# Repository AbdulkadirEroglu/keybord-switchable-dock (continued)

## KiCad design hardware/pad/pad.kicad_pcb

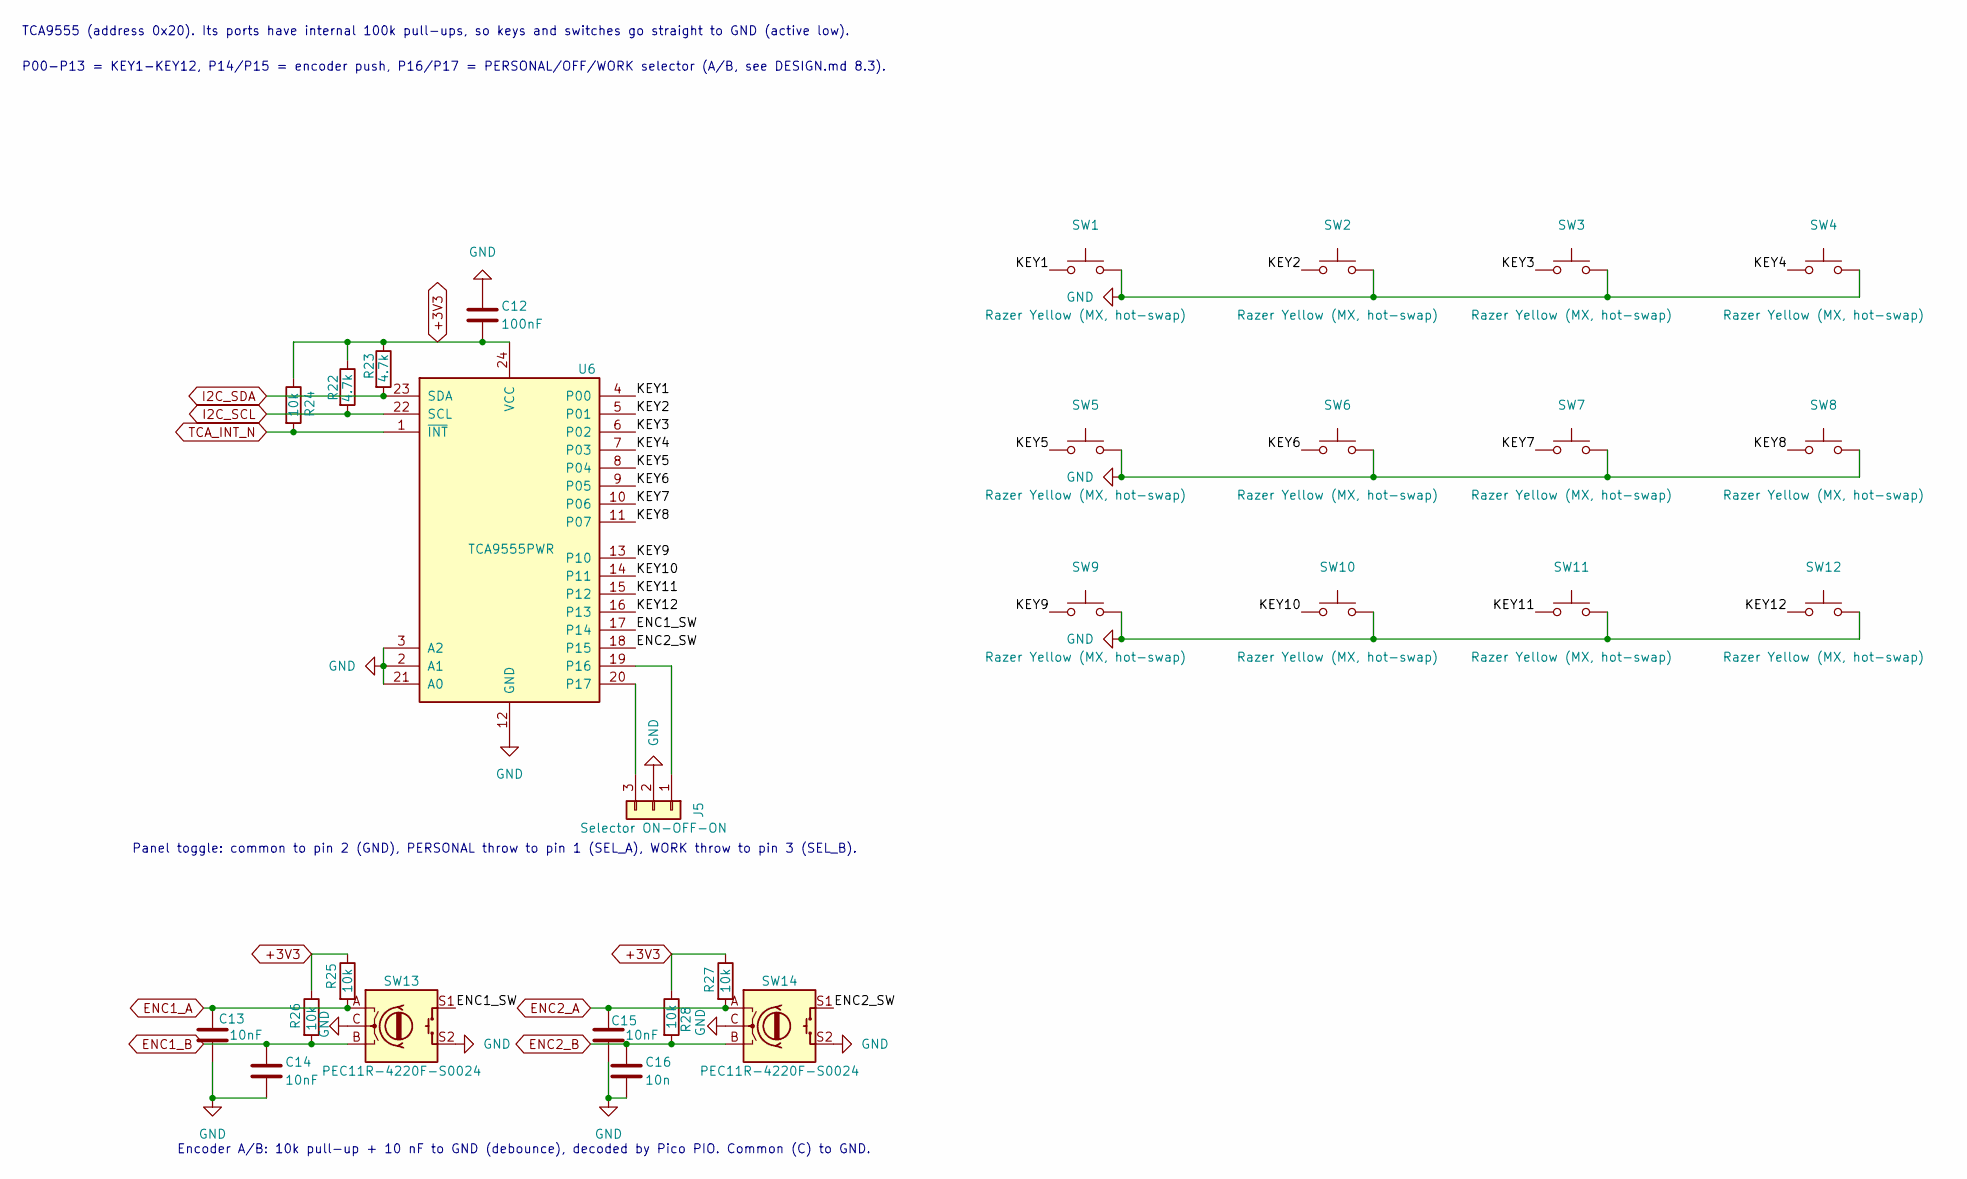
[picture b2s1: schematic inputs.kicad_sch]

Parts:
C12: 100nF; C_0805_2012Metric_Pad1.18x1.45mm_HandSolder
C13, C14, C15: 10nF; C_0805_2012Metric_Pad1.18x1.45mm_HandSolder
C16: 10n; C_0805_2012Metric_Pad1.18x1.45mm_HandSolder
J5: Selector ON-OFF-ON; JST_XH_B3B-XH-A_1x03_P2.50mm_Vertical
R22, R23: 4.7k; R_0805_2012Metric_Pad1.20x1.40mm_HandSolder
R24, R25, R26, R27, R28: 10k; R_0805_2012Metric_Pad1.20x1.40mm_HandSolder
SW1, SW2, SW3, SW4, SW5, SW6, SW7, SW8, SW9, SW10, SW11, SW12: Razer Yellow (MX, hot-swap); SW_MX_Hotswap_Kailh
SW13, SW14: PEC11R-4220F-S0024; RotaryEncoder_Bourns_PEC11R-4xxxF-S_Vertical
U6: TCA9555PWR; TSSOP-24_4.4x7.8mm_P0.65mm

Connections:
+3V3: C12.2, R22.1, R23.1, R24.1, R25.1, R26.1, R27.1, R28.1, U6.24 (VCC); also elsewhere on the board
/INPUTS/ENC1_SW: SW13.S1, U6.17 (P14)
/INPUTS/ENC2_SW: SW14.S1, U6.18 (P15)
/INPUTS/KEY1: SW1.1, U6.4 (P00)
/INPUTS/KEY2: SW2.1, U6.5 (P01)
/INPUTS/KEY3: SW3.1, U6.6 (P02)
/INPUTS/KEY4: SW4.1, U6.7 (P03)
/INPUTS/KEY5: SW5.1, U6.8 (P04)
/INPUTS/KEY6: SW6.1, U6.9 (P05)
/INPUTS/KEY7: SW7.1, U6.10 (P06)
/INPUTS/KEY8: SW8.1, U6.11 (P07)
/INPUTS/KEY9: SW9.1, U6.13 (P10)
/INPUTS/KEY10: SW10.1, U6.14 (P11)
/INPUTS/KEY11: SW11.1, U6.15 (P12)
/INPUTS/KEY12: SW12.1, U6.16 (P13)
ENC1_A: C13.1, R25.2, SW13.A; also elsewhere on the board
ENC1_B: C14.1, R26.2, SW13.B; also elsewhere on the board
ENC2_A: C15.1, R27.2, SW14.A; also elsewhere on the board
ENC2_B: C16.1, R28.2, SW14.B; also elsewhere on the board
GND: C12.1, C13.2, C14.2, C15.2, C16.2, J5.2, SW1.2, SW2.2, SW3.2, SW4.2, SW5.2, SW6.2, SW7.2, SW8.2, SW9.2, SW10.2, SW11.2, SW12.2, SW13.C, SW13.S2, SW14.C, SW14.S2, U6.2 (A1), U6.3 (A2), U6.12 (GND), U6.21 (A0); also elsewhere on the board
I2C_SCL: R22.2, U6.22 (SCL); also elsewhere on the board
I2C_SDA: R23.2, U6.23 (SDA); also elsewhere on the board
unnamed: J5.1, U6.19 (P16)
unnamed: J5.3, U6.20 (P17)
TCA_INT_N: R24.2, U6.1 (~INT); also elsewhere on the board

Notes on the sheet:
P00-P13 = KEY1-KEY12, P14/P15 = encoder push, P16/P17 = PERSONAL/OFF/WORK selector (A/B, see DESIGN.md 8.3).
Encoder A/B: 10k pull-up + 10 nF to GND (debounce), decoded by Pico PIO. Common (C) to GND.
TCA9555 (address 0x20). Its ports have internal 100k pull-ups, so keys and switches go straight to GND (active low).
Panel toggle: common to pin 2 (GND), PERSONAL throw to pin 1 (SEL_A), WORK throw to pin 3 (SEL_B).

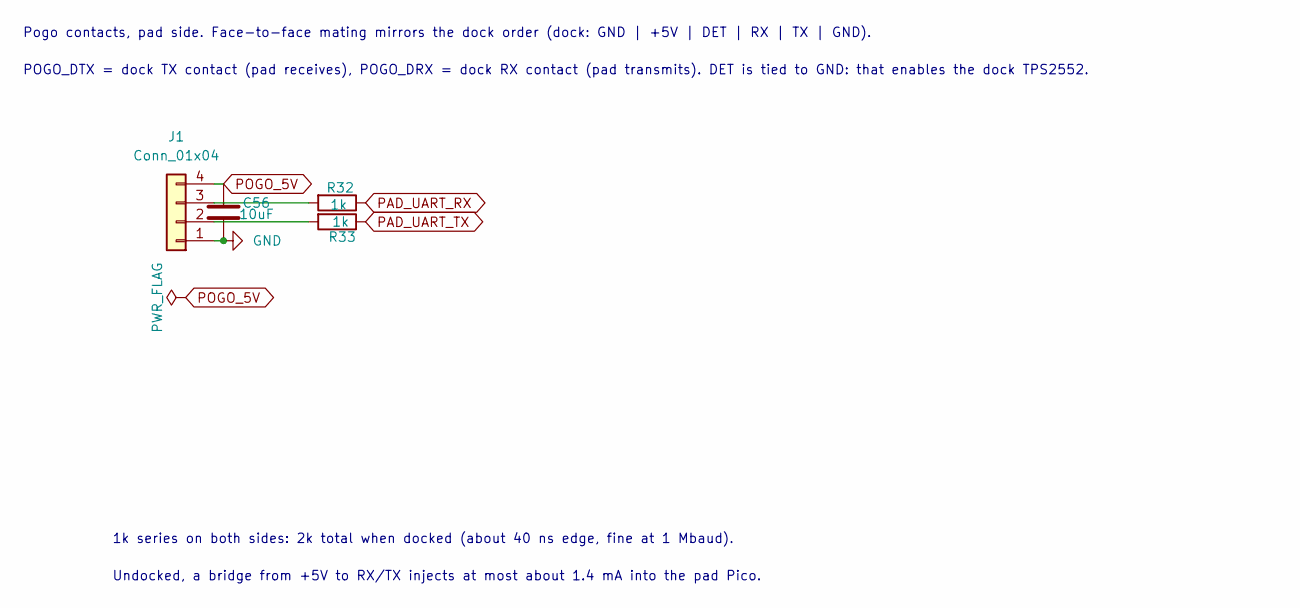
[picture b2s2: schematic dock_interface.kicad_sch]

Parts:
C56: 10uF; C_0805_2012Metric_Pad1.18x1.45mm_HandSolder
J1: Conn_01x04; JST_XH_S4B-XH-A_1x04_P2.50mm_Horizontal
R32, R33: 1k; R_0805_2012Metric_Pad1.20x1.40mm_HandSolder

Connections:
GND: C56.1, J1.1; also elsewhere on the board
unnamed: J1.2, R33.2
unnamed: J1.3, R32.2
PAD_UART_RX: R32.1; also elsewhere on the board
PAD_UART_TX: R33.1; also elsewhere on the board
POGO_5V: C56.2, J1.4; also elsewhere on the board

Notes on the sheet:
Undocked, a bridge from +5V to RX/TX injects at most about 1.4 mA into the pad Pico.
Pogo contacts, pad side. Face-to-face mating mirrors the dock order (dock: GND | +5V | DET | RX | TX | GND).
POGO_DTX = dock TX contact (pad receives), POGO_DRX = dock RX contact (pad transmits). DET is tied to GND: that enables the dock TPS2552.
1k series on both sides: 2k total when docked (about 40 ns edge, fine at 1 Mbaud).

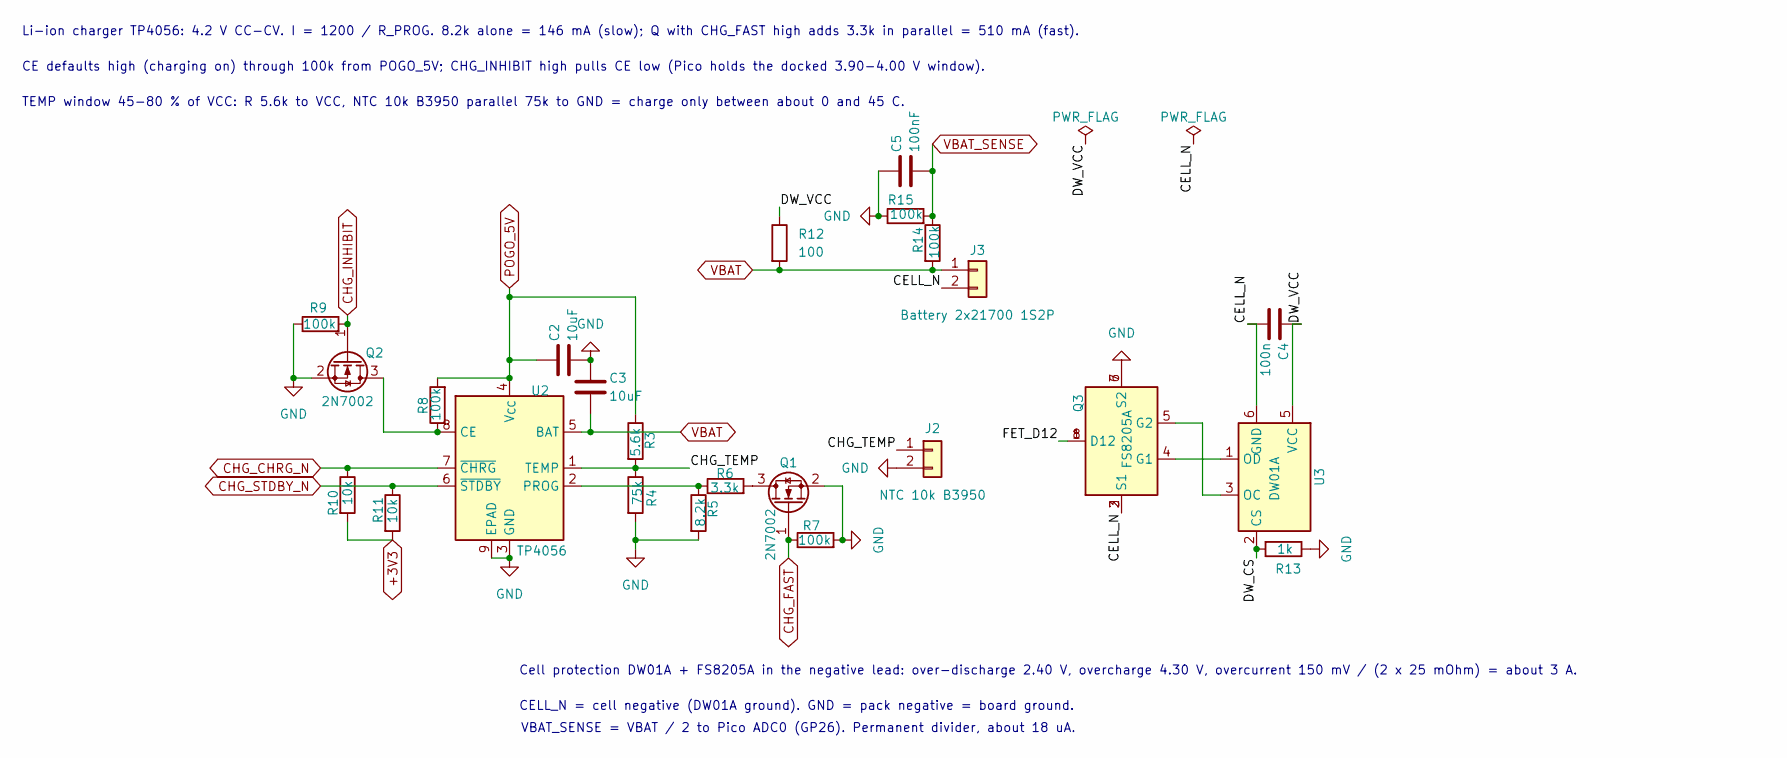
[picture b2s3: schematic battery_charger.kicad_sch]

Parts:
C2, C3: 10uF; C_0805_2012Metric_Pad1.18x1.45mm_HandSolder
C4: 100n; C_0805_2012Metric_Pad1.18x1.45mm_HandSolder
C5: 100nF; C_0805_2012Metric_Pad1.18x1.45mm_HandSolder
J2: NTC 10k B3950; JST_XH_S2B-XH-A_1x02_P2.50mm_Horizontal
J3: Battery 2x21700 1S2P; JST_XH_S2B-XH-A_1x02_P2.50mm_Horizontal
Q1, Q2: 2N7002; SOT-23
Q3: FS8205A; TSSOP-8_4.4x3mm_P0.65mm
R3: 5.6k; R_0805_2012Metric_Pad1.20x1.40mm_HandSolder
R4: 75k; R_0805_2012Metric_Pad1.20x1.40mm_HandSolder
R5: 8.2k; R_0805_2012Metric_Pad1.20x1.40mm_HandSolder
R6: 3.3k; R_0805_2012Metric_Pad1.20x1.40mm_HandSolder
R7, R8, R9, R14, R15: 100k; R_0805_2012Metric_Pad1.20x1.40mm_HandSolder
R10, R11: 10k; R_0805_2012Metric_Pad1.20x1.40mm_HandSolder
R12: 100; R_0805_2012Metric_Pad1.20x1.40mm_HandSolder
R13: 1k; R_0805_2012Metric_Pad1.20x1.40mm_HandSolder
U2: TP4056; SOIC-8-1EP_3.9x4.9mm_HandSolder
U3: DW01A; SOT-23-6

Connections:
+3V3: R10.2, R11.2; also elsewhere on the board
/BATTERY_CHARGER/CELL_N: C4.2, J3.2, Q3.2 (S1), Q3.3 (S1), U3.6 (GND)
/BATTERY_CHARGER/CHG_TEMP: J2.1, R3.2, R4.1, U2.1 (TEMP)
/BATTERY_CHARGER/DW_CS: R13.2, U3.2 (CS)
/BATTERY_CHARGER/DW_VCC: C4.1, R12.1, U3.5 (VCC)
/BATTERY_CHARGER/FET_D12: Q3.1 (D12), Q3.8 (D12)
CHG_CHRG_N: R10.1, U2.7 (~CHRG); also elsewhere on the board
CHG_FAST: Q1.1 (G), R7.1; also elsewhere on the board
CHG_INHIBIT: Q2.1 (G), R9.2; also elsewhere on the board
CHG_STDBY_N: R11.1, U2.6 (~STDBY); also elsewhere on the board
GND: C2.2, C3.1, C5.1, J2.2, Q1.2 (S), Q2.2 (S), Q3.6 (S2), Q3.7 (S2), R4.2, R5.2, R7.2, R9.1, R13.1, R15.1, U2.3 (GND), U2.9 (EPAD); also elsewhere on the board
unnamed: Q1.3 (D), R6.2
unnamed: Q2.3 (D), R8.1, U2.8 (CE)
unnamed: Q3.4 (G1), U3.1 (OD)
unnamed: Q3.5 (G2), U3.3 (OC)
unnamed: R5.1, R6.1, U2.2 (PROG)
POGO_5V: C2.1, R3.1, R8.2, U2.4 (V_{CC}); also elsewhere on the board
VBAT: C3.2, J3.1, R12.2, R14.2, U2.5 (BAT); also elsewhere on the board
VBAT_SENSE: C5.2, R14.1, R15.2; also elsewhere on the board

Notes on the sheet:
CELL_N = cell negative (DW01A ground). GND = pack negative = board ground.
TEMP window 45-80 % of VCC: R 5.6k to VCC, NTC 10k B3950 parallel 75k to GND = charge only between about 0 and 45 C.
CE defaults high (charging on) through 100k from POGO_5V; CHG_INHIBIT high pulls CE low (Pico holds the docked 3.90-4.00 V window).
Cell protection DW01A + FS8205A in the negative lead: over-discharge 2.40 V, overcharge 4.30 V, overcurrent 150 mV / (2 x 25 mOhm) = about 3 A.
Li-ion charger TP4056: 4.2 V CC-CV. I = 1200 / R_PROG. 8.2k alone = 146 mA (slow); Q with CHG_FAST high adds 3.3k in parallel = 510 mA (fast).
VBAT_SENSE = VBAT / 2 to Pico ADC0 (GP26). Permanent divider, about 18 uA.

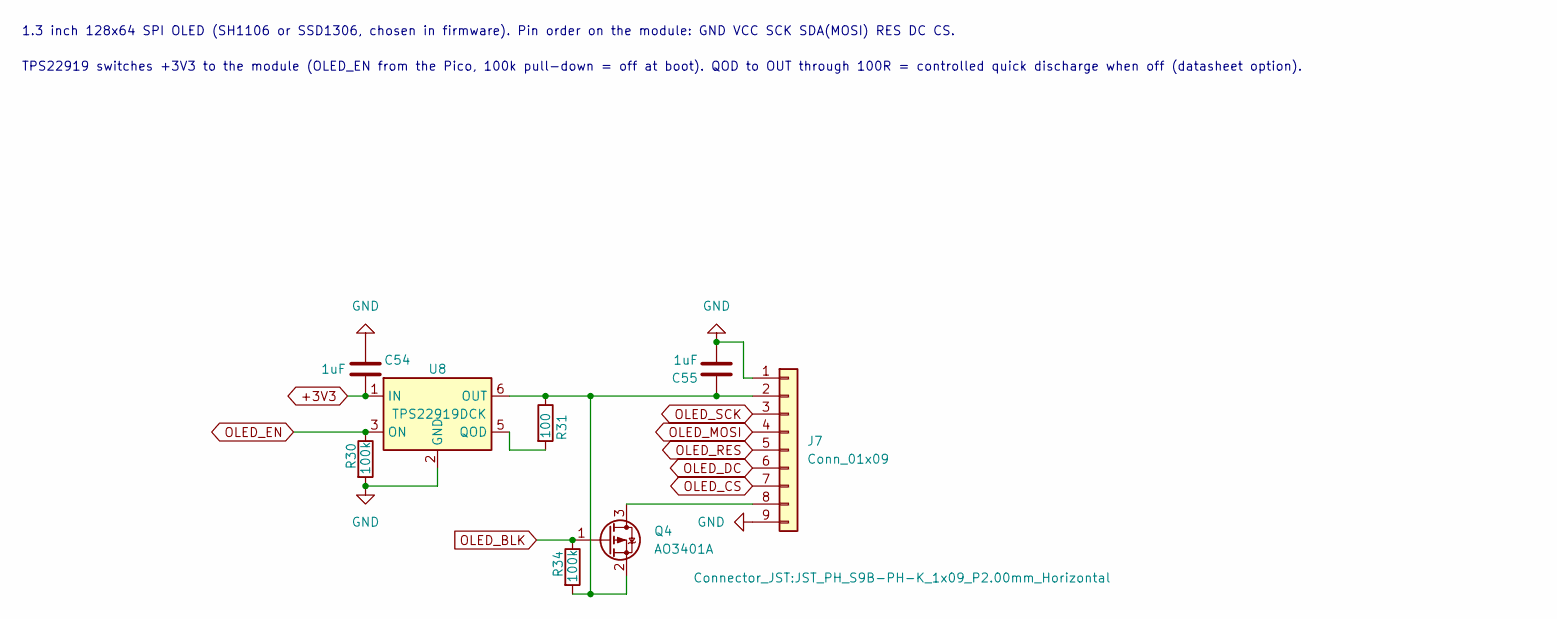
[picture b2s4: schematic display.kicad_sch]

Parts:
C54, C55: 1uF; C_0805_2012Metric_Pad1.18x1.45mm_HandSolder
J7: Conn_01x09; JST_PH_S9B-PH-K_1x09_P2.00mm_Horizontal
Q4: AO3401A; SOT-23
R30, R34: 100k; R_0805_2012Metric_Pad1.20x1.40mm_HandSolder
R31: 100; R_0805_2012Metric_Pad1.20x1.40mm_HandSolder
U8: TPS22919DCK; SOT-363_SC-70-6

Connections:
+3V3: C54.2, U8.1 (IN); also elsewhere on the board
GND: C54.1, C55.2, J7.1, J7.9, R30.2, U8.2 (GND); also elsewhere on the board
unnamed: C55.1, J7.2, Q4.2 (S), R31.1, R34.2, U8.6 (OUT)
unnamed: J7.8, Q4.3 (D)
unnamed: R31.2, U8.5 (QOD)
OLED_BLK: Q4.1 (G), R34.1; also elsewhere on the board
OLED_CS: J7.7; also elsewhere on the board
OLED_DC: J7.6; also elsewhere on the board
OLED_EN: R30.1, U8.3 (ON); also elsewhere on the board
OLED_MOSI: J7.4; also elsewhere on the board
OLED_RES: J7.5; also elsewhere on the board
OLED_SCK: J7.3; also elsewhere on the board

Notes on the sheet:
1.3 inch 128x64 SPI OLED (SH1106 or SSD1306, chosen in firmware). Pin order on the module: GND VCC SCK SDA(MOSI) RES DC CS.
TPS22919 switches +3V3 to the module (OLED_EN from the Pico, 100k pull-down = off at boot). QOD to OUT through 100R = controlled quick discharge when off (datasheet option).

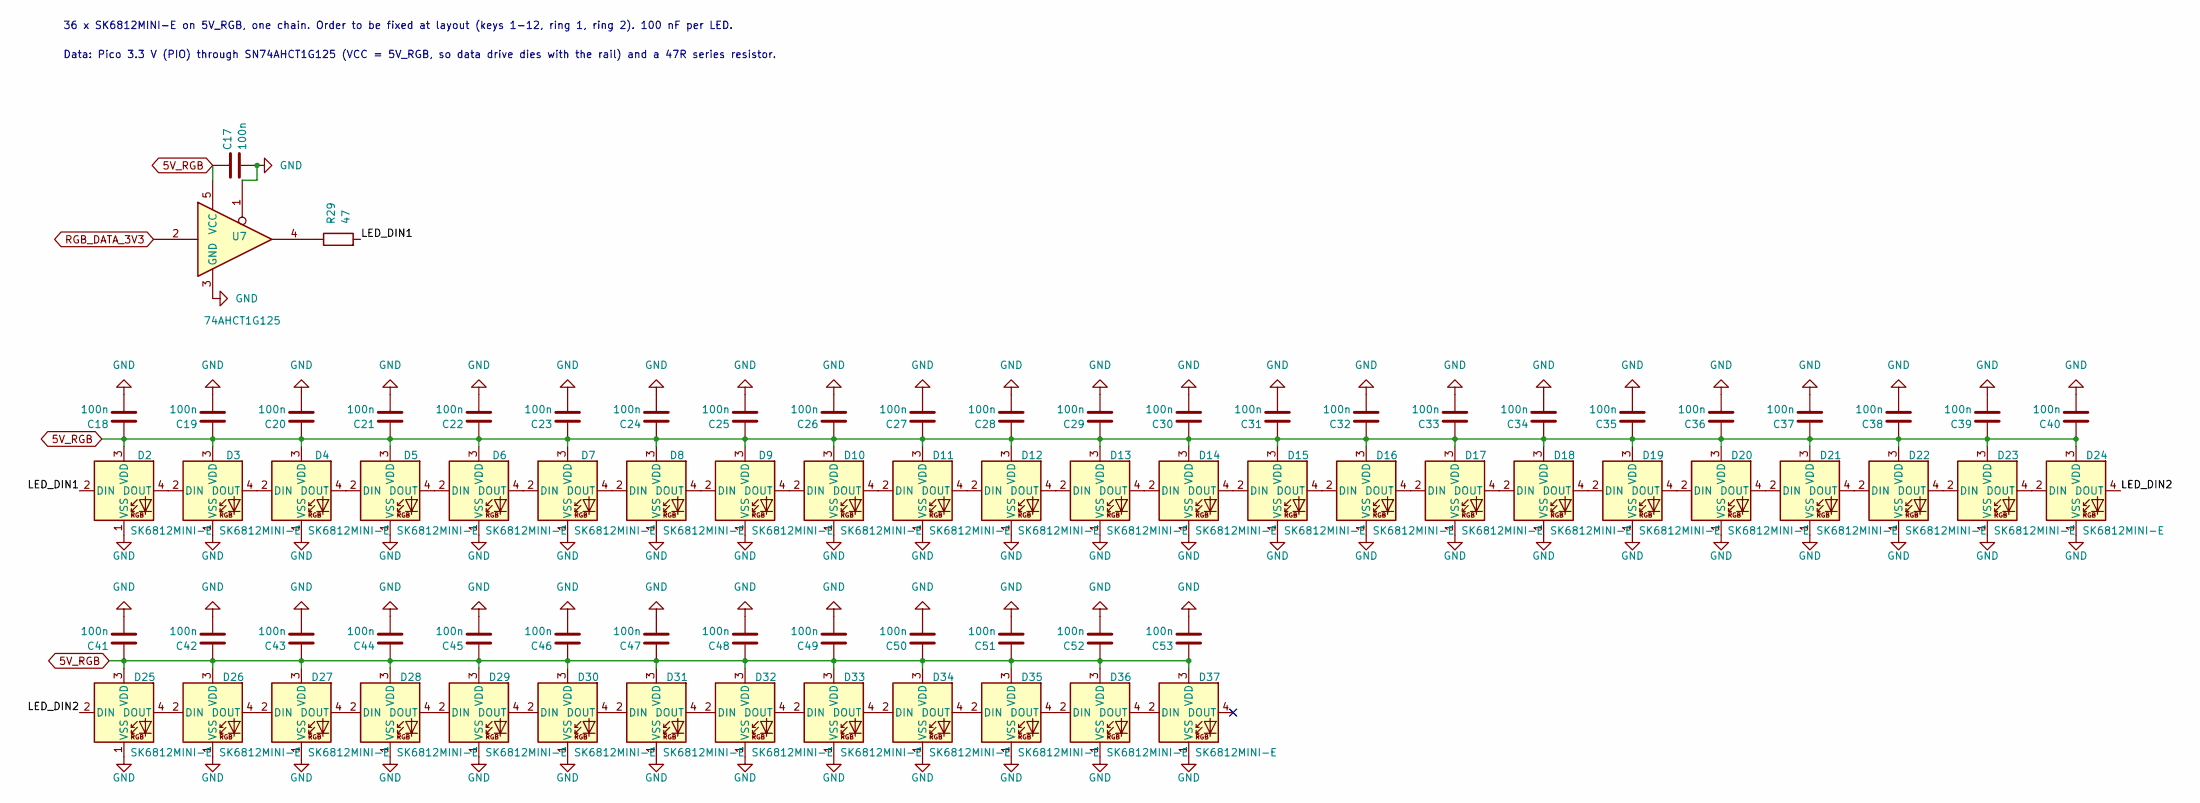
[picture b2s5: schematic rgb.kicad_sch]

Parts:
C17, C18, C19, C20, C21, C22, C23, C24, C25, C26, C27, C28, C29, C30, C31, C32, C33, C34, C35, C36, C37, C38, C39, C40, C41, C42, C43, C44, C45, C46, C47, C48, C49, C50, C51, C52, C53: 100n; C_0805_2012Metric_Pad1.18x1.45mm_HandSolder
D2, D3, D4, D5, D6, D7, D8, D9, D10, D11, D12, D13, D14, D15, D16, D17, D18, D19, D20, D21, D22, D23, D24, D25, D26, D27, D28, D29, D30, D31, D32, D33, D34, D35, D36, D37: SK6812MINI-E; LED_SK6812MINI-E_3.2x2.8mm_P1.5mm_ReverseMount
R29: 47; R_0805_2012Metric_Pad1.20x1.40mm_HandSolder
U7: 74AHCT1G125; SOT-23-5

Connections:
5V_RGB: C17.1, C18.1, C19.1, C20.1, C21.1, C22.1, C23.1, C24.1, C25.1, C26.1, C27.1, C28.1, C29.1, C30.1, C31.1, C32.1, C33.1, C34.1, C35.1, C36.1, C37.1, C38.1, C39.1, C40.1, C41.1, C42.1, C43.1, C44.1, C45.1, C46.1, C47.1, C48.1, C49.1, C50.1, C51.1, C52.1, C53.1, D2.3 (VDD), D3.3 (VDD), D4.3 (VDD), D5.3 (VDD), D6.3 (VDD), D7.3 (VDD), D8.3 (VDD), D9.3 (VDD), D10.3 (VDD), D11.3 (VDD), D12.3 (VDD), D13.3 (VDD), D14.3 (VDD), D15.3 (VDD), D16.3 (VDD), D17.3 (VDD), D18.3 (VDD), D19.3 (VDD), D20.3 (VDD), D21.3 (VDD), D22.3 (VDD), D23.3 (VDD), D24.3 (VDD), D25.3 (VDD), D26.3 (VDD), D27.3 (VDD), D28.3 (VDD), D29.3 (VDD), D30.3 (VDD), D31.3 (VDD), D32.3 (VDD), D33.3 (VDD), D34.3 (VDD), D35.3 (VDD), D36.3 (VDD), D37.3 (VDD), U7.5 (VCC); also elsewhere on the board
/RGB/LED_DIN1: D2.2 (DIN), R29.2
/RGB/LED_DIN2: D24.4 (DOUT), D25.2 (DIN)
GND: C17.2, C18.2, C19.2, C20.2, C21.2, C22.2, C23.2, C24.2, C25.2, C26.2, C27.2, C28.2, C29.2, C30.2, C31.2, C32.2, C33.2, C34.2, C35.2, C36.2, C37.2, C38.2, C39.2, C40.2, C41.2, C42.2, C43.2, C44.2, C45.2, C46.2, C47.2, C48.2, C49.2, C50.2, C51.2, C52.2, C53.2, D2.1 (VSS), D3.1 (VSS), D4.1 (VSS), D5.1 (VSS), D6.1 (VSS), D7.1 (VSS), D8.1 (VSS), D9.1 (VSS), D10.1 (VSS), D11.1 (VSS), D12.1 (VSS), D13.1 (VSS), D14.1 (VSS), D15.1 (VSS), D16.1 (VSS), D17.1 (VSS), D18.1 (VSS), D19.1 (VSS), D20.1 (VSS), D21.1 (VSS), D22.1 (VSS), D23.1 (VSS), D24.1 (VSS), D25.1 (VSS), D26.1 (VSS), D27.1 (VSS), D28.1 (VSS), D29.1 (VSS), D30.1 (VSS), D31.1 (VSS), D32.1 (VSS), D33.1 (VSS), D34.1 (VSS), D35.1 (VSS), D36.1 (VSS), D37.1 (VSS), U7.1, U7.3 (GND); also elsewhere on the board
unnamed: D2.4 (DOUT), D3.2 (DIN)
unnamed: D3.4 (DOUT), D4.2 (DIN)
unnamed: D4.4 (DOUT), D5.2 (DIN)
unnamed: D5.4 (DOUT), D6.2 (DIN)
unnamed: D6.4 (DOUT), D7.2 (DIN)
unnamed: D7.4 (DOUT), D8.2 (DIN)
unnamed: D8.4 (DOUT), D9.2 (DIN)
unnamed: D9.4 (DOUT), D10.2 (DIN)
unnamed: D10.4 (DOUT), D11.2 (DIN)
unnamed: D11.4 (DOUT), D12.2 (DIN)
unnamed: D12.4 (DOUT), D13.2 (DIN)
unnamed: D13.4 (DOUT), D14.2 (DIN)
unnamed: D14.4 (DOUT), D15.2 (DIN)
unnamed: D15.4 (DOUT), D16.2 (DIN)
unnamed: D16.4 (DOUT), D17.2 (DIN)
unnamed: D17.4 (DOUT), D18.2 (DIN)
unnamed: D18.4 (DOUT), D19.2 (DIN)
unnamed: D19.4 (DOUT), D20.2 (DIN)
unnamed: D20.4 (DOUT), D21.2 (DIN)
unnamed: D21.4 (DOUT), D22.2 (DIN)
unnamed: D22.4 (DOUT), D23.2 (DIN)
unnamed: D23.4 (DOUT), D24.2 (DIN)
unnamed: D25.4 (DOUT), D26.2 (DIN)
unnamed: D26.4 (DOUT), D27.2 (DIN)
unnamed: D27.4 (DOUT), D28.2 (DIN)
unnamed: D28.4 (DOUT), D29.2 (DIN)
unnamed: D29.4 (DOUT), D30.2 (DIN)
unnamed: D30.4 (DOUT), D31.2 (DIN)
unnamed: D31.4 (DOUT), D32.2 (DIN)
unnamed: D32.4 (DOUT), D33.2 (DIN)
unnamed: D33.4 (DOUT), D34.2 (DIN)
unnamed: D34.4 (DOUT), D35.2 (DIN)
unnamed: D35.4 (DOUT), D36.2 (DIN)
unnamed: D36.4 (DOUT), D37.2 (DIN)
unnamed: R29.1, U7.4
RGB_DATA_3V3: U7.2; also elsewhere on the board

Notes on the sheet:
Data: Pico 3.3 V (PIO) through SN74AHCT1G125 (VCC = 5V_RGB, so data drive dies with the rail) and a 47R series resistor.
36 x SK6812MINI-E on 5V_RGB, one chain. Order to be fixed at layout (keys 1-12, ring 1, ring 2). 100 nF per LED.

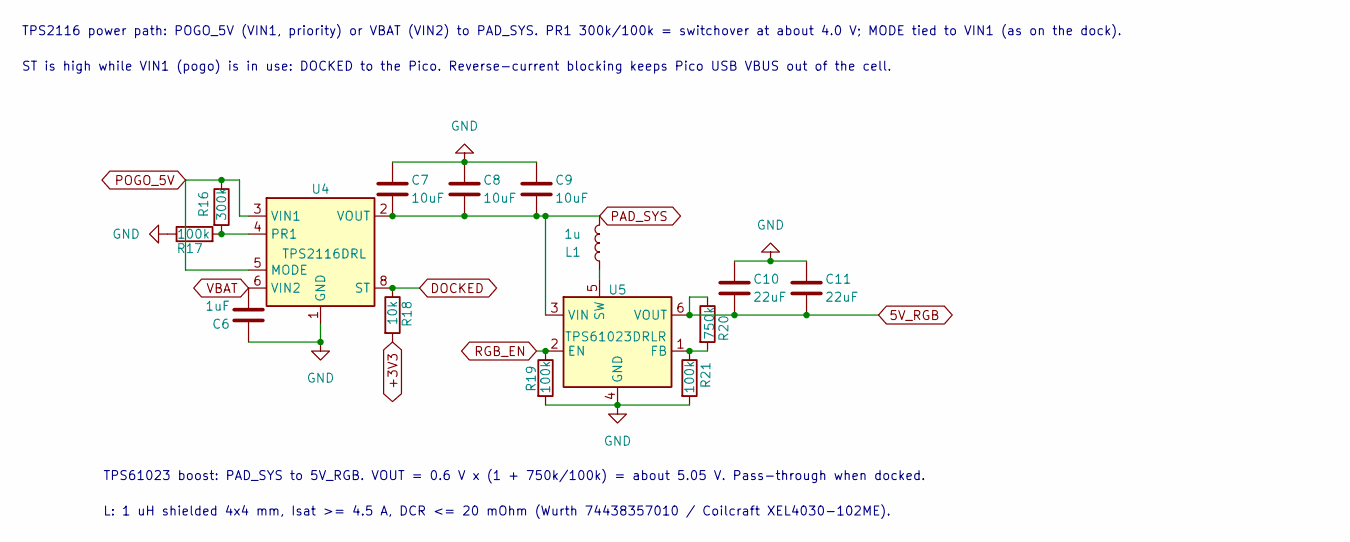
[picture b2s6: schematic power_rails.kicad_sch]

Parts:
C6: 1uF; C_0805_2012Metric_Pad1.18x1.45mm_HandSolder
C7, C8: 10uF; C_0805_2012Metric_Pad1.18x1.45mm_HandSolder
C9: 10uF; C_1206_3216Metric_Pad1.33x1.80mm_HandSolder
C10, C11: 22uF; C_1206_3216Metric_Pad1.33x1.80mm_HandSolder
L1: 1u; L_Coilcraft_XxL4030
R16: 300k; R_0805_2012Metric_Pad1.20x1.40mm_HandSolder
R17, R19, R21: 100k; R_0805_2012Metric_Pad1.20x1.40mm_HandSolder
R18: 10k; R_0805_2012Metric_Pad1.20x1.40mm_HandSolder
R20: 750k; R_0805_2012Metric_Pad1.20x1.40mm_HandSolder
U4: TPS2116DRL; SOT-583-8_HandSolder
U5: TPS61023DRLR; SOT-563-6_HandSolder

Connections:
5V_RGB: C10.2, C11.2, R20.1, U5.6 (VOUT); also elsewhere on the board
+3V3: R18.2; also elsewhere on the board
DOCKED: R18.1, U4.8 (ST); also elsewhere on the board
GND: C6.1, C7.1, C8.1, C9.1, C10.1, C11.1, R17.1, R19.2, R21.2, U4.1 (GND), U5.4 (GND); also elsewhere on the board
unnamed: R16.2, R17.2, U4.4 (PR1)
unnamed: R20.2, R21.1, U5.1 (FB)
unnamed: L1.1, U5.5 (SW)
PAD_SYS: C7.2, C8.2, C9.2, L1.2, U4.2 (VOUT), U4.7 (VOUT), U5.3 (VIN); also elsewhere on the board
POGO_5V: R16.1, U4.3 (VIN1), U4.5 (MODE); also elsewhere on the board
RGB_EN: R19.1, U5.2 (EN); also elsewhere on the board
VBAT: C6.2, U4.6 (VIN2); also elsewhere on the board

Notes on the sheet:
L: 1 uH shielded 4x4 mm, Isat >= 4.5 A, DCR <= 20 mOhm (Wurth 74438357010 / Coilcraft XEL4030-102ME).
ST is high while VIN1 (pogo) is in use: DOCKED to the Pico. Reverse-current blocking keeps Pico USB VBUS out of the cell.
TPS2116 power path: POGO_5V (VIN1, priority) or VBAT (VIN2) to PAD_SYS. PR1 300k/100k = switchover at about 4.0 V; MODE tied to VIN1 (as on the dock).
TPS61023 boost: PAD_SYS to 5V_RGB. VOUT = 0.6 V x (1 + 750k/100k) = about 5.05 V. Pass-through when docked.

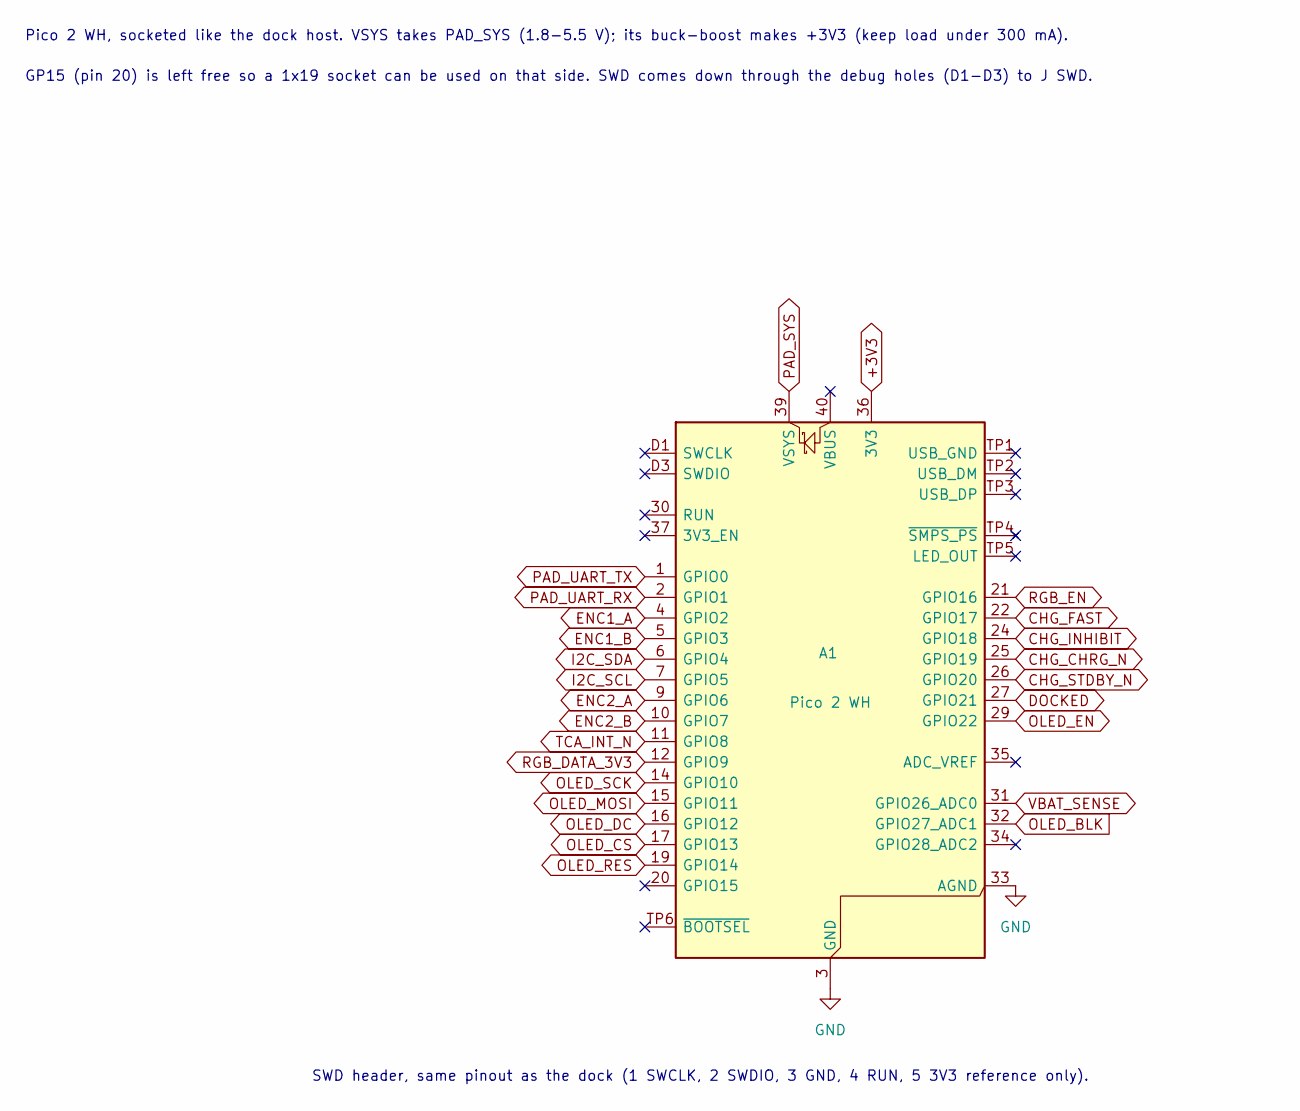
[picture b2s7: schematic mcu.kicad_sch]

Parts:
A1: Pico 2 WH; RaspberryPi_Pico2W_Socket_NoSWD

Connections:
+3V3: A1.36 (3V3); also elsewhere on the board
CHG_CHRG_N: A1.25 (GPIO19); also elsewhere on the board
CHG_FAST: A1.22 (GPIO17); also elsewhere on the board
CHG_INHIBIT: A1.24 (GPIO18); also elsewhere on the board
CHG_STDBY_N: A1.26 (GPIO20); also elsewhere on the board
DOCKED: A1.27 (GPIO21); also elsewhere on the board
ENC1_A: A1.4 (GPIO2); also elsewhere on the board
ENC1_B: A1.5 (GPIO3); also elsewhere on the board
ENC2_A: A1.9 (GPIO6); also elsewhere on the board
ENC2_B: A1.10 (GPIO7); also elsewhere on the board
GND: A1.3 (GND), A1.8 (GND), A1.13 (GND), A1.18 (GND), A1.23 (GND), A1.28 (GND), A1.33 (AGND), A1.38 (GND), A1.D2 (GND); also elsewhere on the board
I2C_SCL: A1.7 (GPIO5); also elsewhere on the board
I2C_SDA: A1.6 (GPIO4); also elsewhere on the board
OLED_BLK: A1.32 (GPIO27_ADC1); also elsewhere on the board
OLED_CS: A1.17 (GPIO13); also elsewhere on the board
OLED_DC: A1.16 (GPIO12); also elsewhere on the board
OLED_EN: A1.29 (GPIO22); also elsewhere on the board
OLED_MOSI: A1.15 (GPIO11); also elsewhere on the board
OLED_RES: A1.19 (GPIO14); also elsewhere on the board
OLED_SCK: A1.14 (GPIO10); also elsewhere on the board
PAD_SYS: A1.39 (VSYS); also elsewhere on the board
PAD_UART_RX: A1.2 (GPIO1); also elsewhere on the board
PAD_UART_TX: A1.1 (GPIO0); also elsewhere on the board
RGB_DATA_3V3: A1.12 (GPIO9); also elsewhere on the board
RGB_EN: A1.21 (GPIO16); also elsewhere on the board
TCA_INT_N: A1.11 (GPIO8); also elsewhere on the board
VBAT_SENSE: A1.31 (GPIO26_ADC0); also elsewhere on the board

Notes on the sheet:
GP15 (pin 20) is left free so a 1x19 socket can be used on that side. SWD comes down through the debug holes (D1-D3) to J SWD.
Pico 2 WH, socketed like the dock host. VSYS takes PAD_SYS (1.8-5.5 V); its buck-boost makes +3V3 (keep load under 300 mA).
SWD header, same pinout as the dock (1 SWCLK, 2 SWDIO, 3 GND, 4 RUN, 5 3V3 reference only).

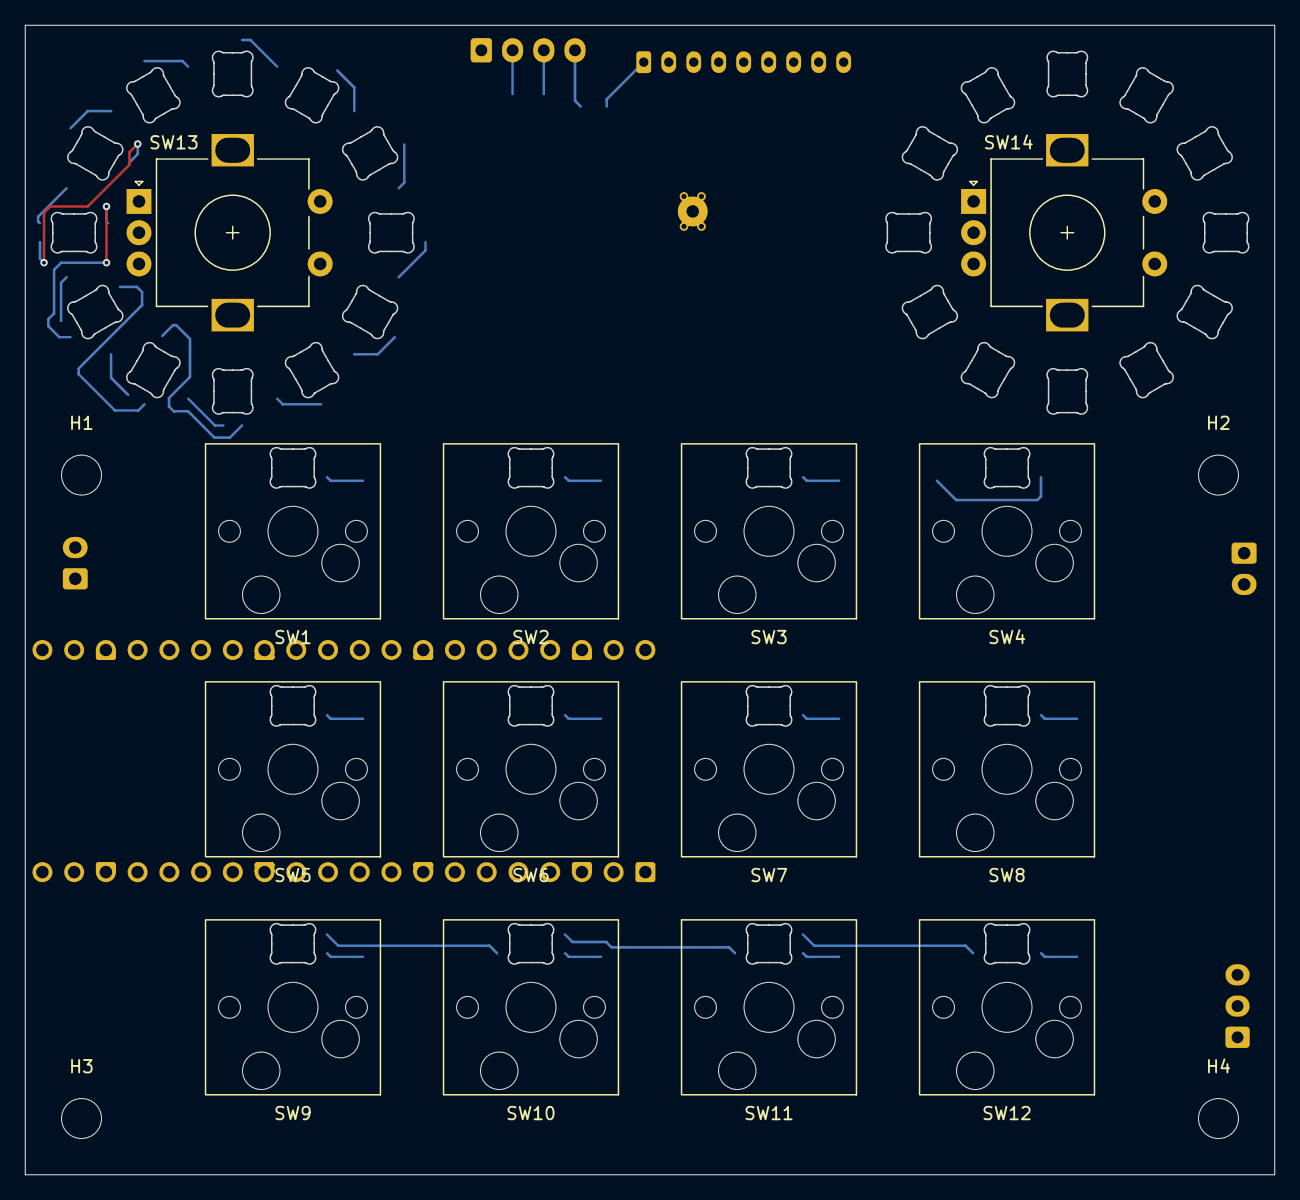
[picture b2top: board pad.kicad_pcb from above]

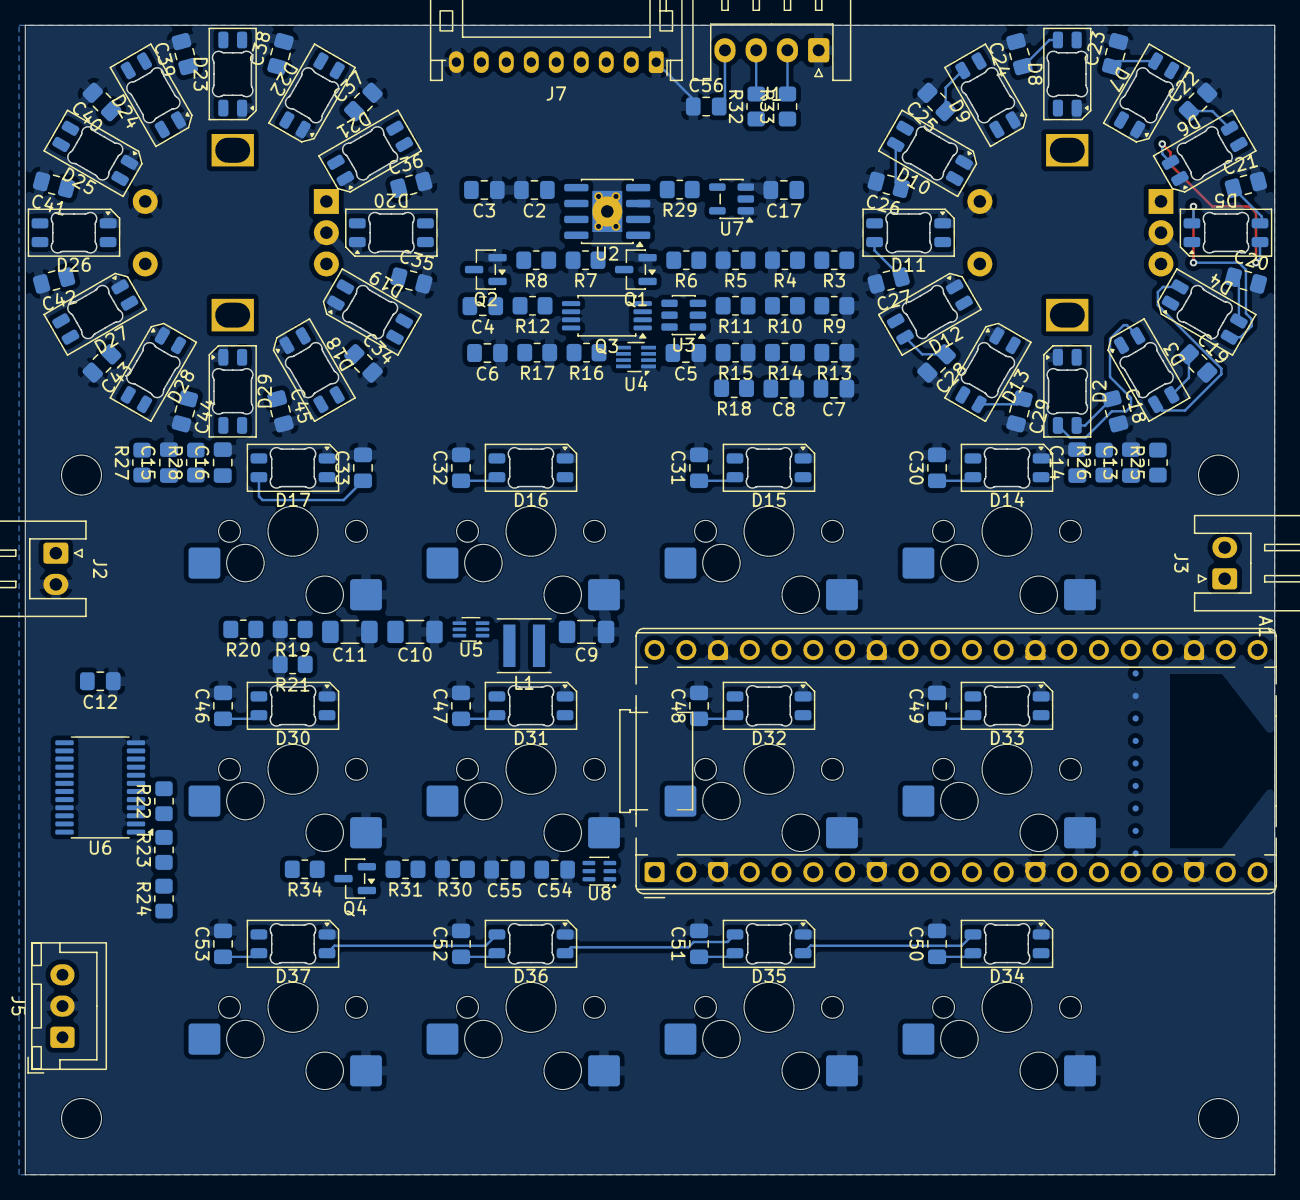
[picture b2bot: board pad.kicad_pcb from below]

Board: 2 copper layers, 100.0 x 92.0 mm, 159 parts (141 on the bottom side), 101 nets.

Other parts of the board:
H1, H2, H3, H4: M3; MountingHole_3.2mm_M3
